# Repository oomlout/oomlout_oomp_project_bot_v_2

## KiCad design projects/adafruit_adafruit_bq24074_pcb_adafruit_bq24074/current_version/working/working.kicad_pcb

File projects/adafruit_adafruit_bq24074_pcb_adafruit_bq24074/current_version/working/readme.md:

# adafruit_bq24074_pcb
 
## summary 
* id: adafruit_adafruit_bq24074_pcb_adafruit_bq24074
* user: adafruit
* name: adafruit_bq24074_pcb
* board: adafruit_bq24074
* repo: https://github.com/adafruit/Adafruit-BQ24074-PCB

* src_file_repo_sch: 
* src_file_repo_sch_link: https://github.com/adafruit/Adafruit-BQ24074-PCB/tree/master/
* full details link: https://github.com/oomlout/oomlout_oomp_project_bot_v_2/tree/main/projects/adafruit_adafruit_bq24074_pcb_adafruit_bq24074/current_version/working  

## schematic  
  
[schematic (pdf)](working_schematic.pdf) 

## pcb  

[board (pdf)](working.pdf)  

## working_bom
| Id | Designator | Footprint | Quantity | Designation | Supplier and ref |  | None | 
| --- | --- | --- | --- | --- | --- | --- | --- | 
| 1 | D2,D4 | SMADIODE | 2 | SK34A |  |  | [''] | 
| 2 | FID3,FID1,FID2 | FIDUCIAL_1MM | 3 | FIDUCIAL_1MM |  |  | [''] | 
| 3 | UNK0.5A0,UNK1.5A0 | SOLDERJUMPER_ARROW_NOPASTE | 2 |  |  |  | [''] | 
| 4 | R10,R8,R11,R2,R7 | 0603-NO | 5 | 10K |  |  | [''] | 
| 5 | JP3 | 1X11_ROUND_76 | 1 |  |  |  | [''] | 
| 6 | X2 | USB_C_CUSB31-CFM2AX-01-X | 1 | USB Type C |  |  | [''] | 
| 7 | R9,R1 | 0603-NO | 2 | 1K |  |  | [''] | 
| 8 | R6,R4 | 0603-NO | 2 | 5.1K |  |  | [''] | 
| 9 | SYSOUT0,BATT0 | JST-PH-2-SMT-RA | 2 | JST 2PH |  |  | [''] | 
| 10 | U$14 | ADAFRUIT_5MM | 1 |  |  |  | [''] | 
| 11 | THERM0,UNK1A0 | SOLDERJUMPER_CLOSEDWIRE | 2 |  |  |  | [''] | 
| 12 | C1,C9,C5,C3,C6,C2,C4 | 0805-NO | 7 | 10uF |  |  | [''] | 
| 13 | R5 | 0603-NO | 1 | 2K |  |  | [''] | 
| 14 | R3 | 0603-NO | 1 | 590 |  |  | [''] | 
| 15 | U$11,U$3,U$12,U$4 | MOUNTINGHOLE_2.5_PLATED | 4 | MOUNTINGHOLE2.5 |  |  | [''] | 
| 16 | X3 | DCJACK_2MM_SMT | 1 | 2.1mm DC |  |  | [''] | 
| 17 | JP2,JP4 | 1X01_OVAL | 2 |  |  |  | [''] | 
| 18 | D3 | CHIPLED_0603 | 1 | RED |  |  | [''] | 
| 19 | X4 | QFN16_3MM | 1 | BQ24074 |  |  | [''] | 
| 20 | JP1 | 1X02_ROUND | 1 |  |  |  | [''] | 
| 21 | D1 | CHIPLED_0603 | 1 | GREEN |  |  | [''] | 
| 22 | SJ2,SJ1 | SOLDERJUMPER_2WAY_OPEN_NOPASTE | 2 |  |  |  | [''] | 
| 23 | U$18 | PCBFEAT-REV-040 | 1 |  |  |  | [''] | 

## bom_schematic
| Ref | Qnty | Value | Cmp name | Footprint | Description | Vendor | DNP | 
| --- | --- | --- | --- | --- | --- | --- | --- | 
| BATT0 | 1 | JST 2PH | JST_2PIN-SMT-RA | working:JST-PH-2-SMT-RA |  |  |  | 
| C1, C2, C3, C4, C5, C6, C9 | 7 | 10uF | CAP_CERAMIC0805-NOOUTLINE | working:0805-NO |  |  |  | 
| D1 | 1 | GREEN | LED0603 | working:CHIPLED_0603 |  |  |  | 
| D2, D4 | 2 | SK34A | DIODE-SCHOTTKYSMA | working:SMADIODE |  |  |  | 
| D3 | 1 | RED | LED0603 | working:CHIPLED_0603 |  |  |  | 
| FID1, FID2, FID3 | 3 | FIDUCIAL_1MM | FIDUCIAL_1MM | working:FIDUCIAL_1MM |  |  |  | 
| JP1 | 1 | HEADER-1X2ROUND | HEADER-1X2ROUND | working:1X02_ROUND |  |  |  | 
| JP2, JP4 | 2 | HEADER-1X1 | HEADER-1X1 | working:1X01_OVAL |  |  |  | 
| JP3 | 1 | HEADER-1X1176MIL | HEADER-1X1176MIL | working:1X11_ROUND_76 |  |  |  | 
| R1, R9 | 2 | 1K | RESISTOR_0603_NOOUT | working:0603-NO |  |  |  | 
| R2, R7, R8, R10, R11 | 5 | 10K | RESISTOR_0603_NOOUT | working:0603-NO |  |  |  | 
| R3 | 1 | 590 | RESISTOR_0603_NOOUT | working:0603-NO |  |  |  | 
| R4, R6 | 2 | 5.1K | RESISTOR_0603_NOOUT | working:0603-NO |  |  |  | 
| R5 | 1 | 2K | RESISTOR_0603_NOOUT | working:0603-NO |  |  |  | 
| SJ1, SJ2 | 2 | SOLDERJUMPER_2WAY | SOLDERJUMPER_2WAY | working:SOLDERJUMPER_2WAY_OPEN_NOPASTE |  |  |  | 
| SYSOUT0 | 1 | JST 2PH | JST_2PIN-SMT-RA | working:JST-PH-2-SMT-RA |  |  |  | 
| THERM0 | 1 | SOLDERJUMPERCLOSED | SOLDERJUMPERCLOSED | working:SOLDERJUMPER_CLOSEDWIRE |  |  |  | 
| U$3, U$4, U$11, U$12 | 4 | MOUNTINGHOLE2.5 | MOUNTINGHOLE2.5 | working:MOUNTINGHOLE_2.5_PLATED |  |  |  | 
| UNK0.5A0 | 1 | SOLDERJUMPER | SOLDERJUMPER | working:SOLDERJUMPER_ARROW_NOPASTE |  |  |  | 
| UNK1.5A0 | 1 | SOLDERJUMPER | SOLDERJUMPER | working:SOLDERJUMPER_ARROW_NOPASTE |  |  |  | 
| UNK1A0 | 1 | SOLDERJUMPERCLOSED | SOLDERJUMPERCLOSED | working:SOLDERJUMPER_CLOSEDWIRE |  |  |  | 
| X2 | 1 | USB Type C | USB_C | working:USB_C_CUSB31-CFM2AX-01-X |  |  |  | 
| X3 | 1 | 2.1mm DC | DCBARRELSMT | working:DCJACK_2MM_SMT |  |  |  | 
| X4 | 1 | BQ24074 | BQ24074 | working:QFN16_3MM |  |  |  | 

## mounting_holes
| x | y | package | value | ref | size | 
| --- | --- | --- | --- | --- | --- | 
| 0.0 | 0.0 | MOUNTINGHOLE_2.5_PLATED | MOUNTINGHOLE2.5 | U$3 | m3 | 
| 0.0 | 27.94 | MOUNTINGHOLE_2.5_PLATED | MOUNTINGHOLE2.5 | U$4 | m3 | 
| 33.02 | 27.94 | MOUNTINGHOLE_2.5_PLATED | MOUNTINGHOLE2.5 | U$11 | m3 | 
| 33.02 | 0.0 | MOUNTINGHOLE_2.5_PLATED | MOUNTINGHOLE2.5 | U$12 | m3 |

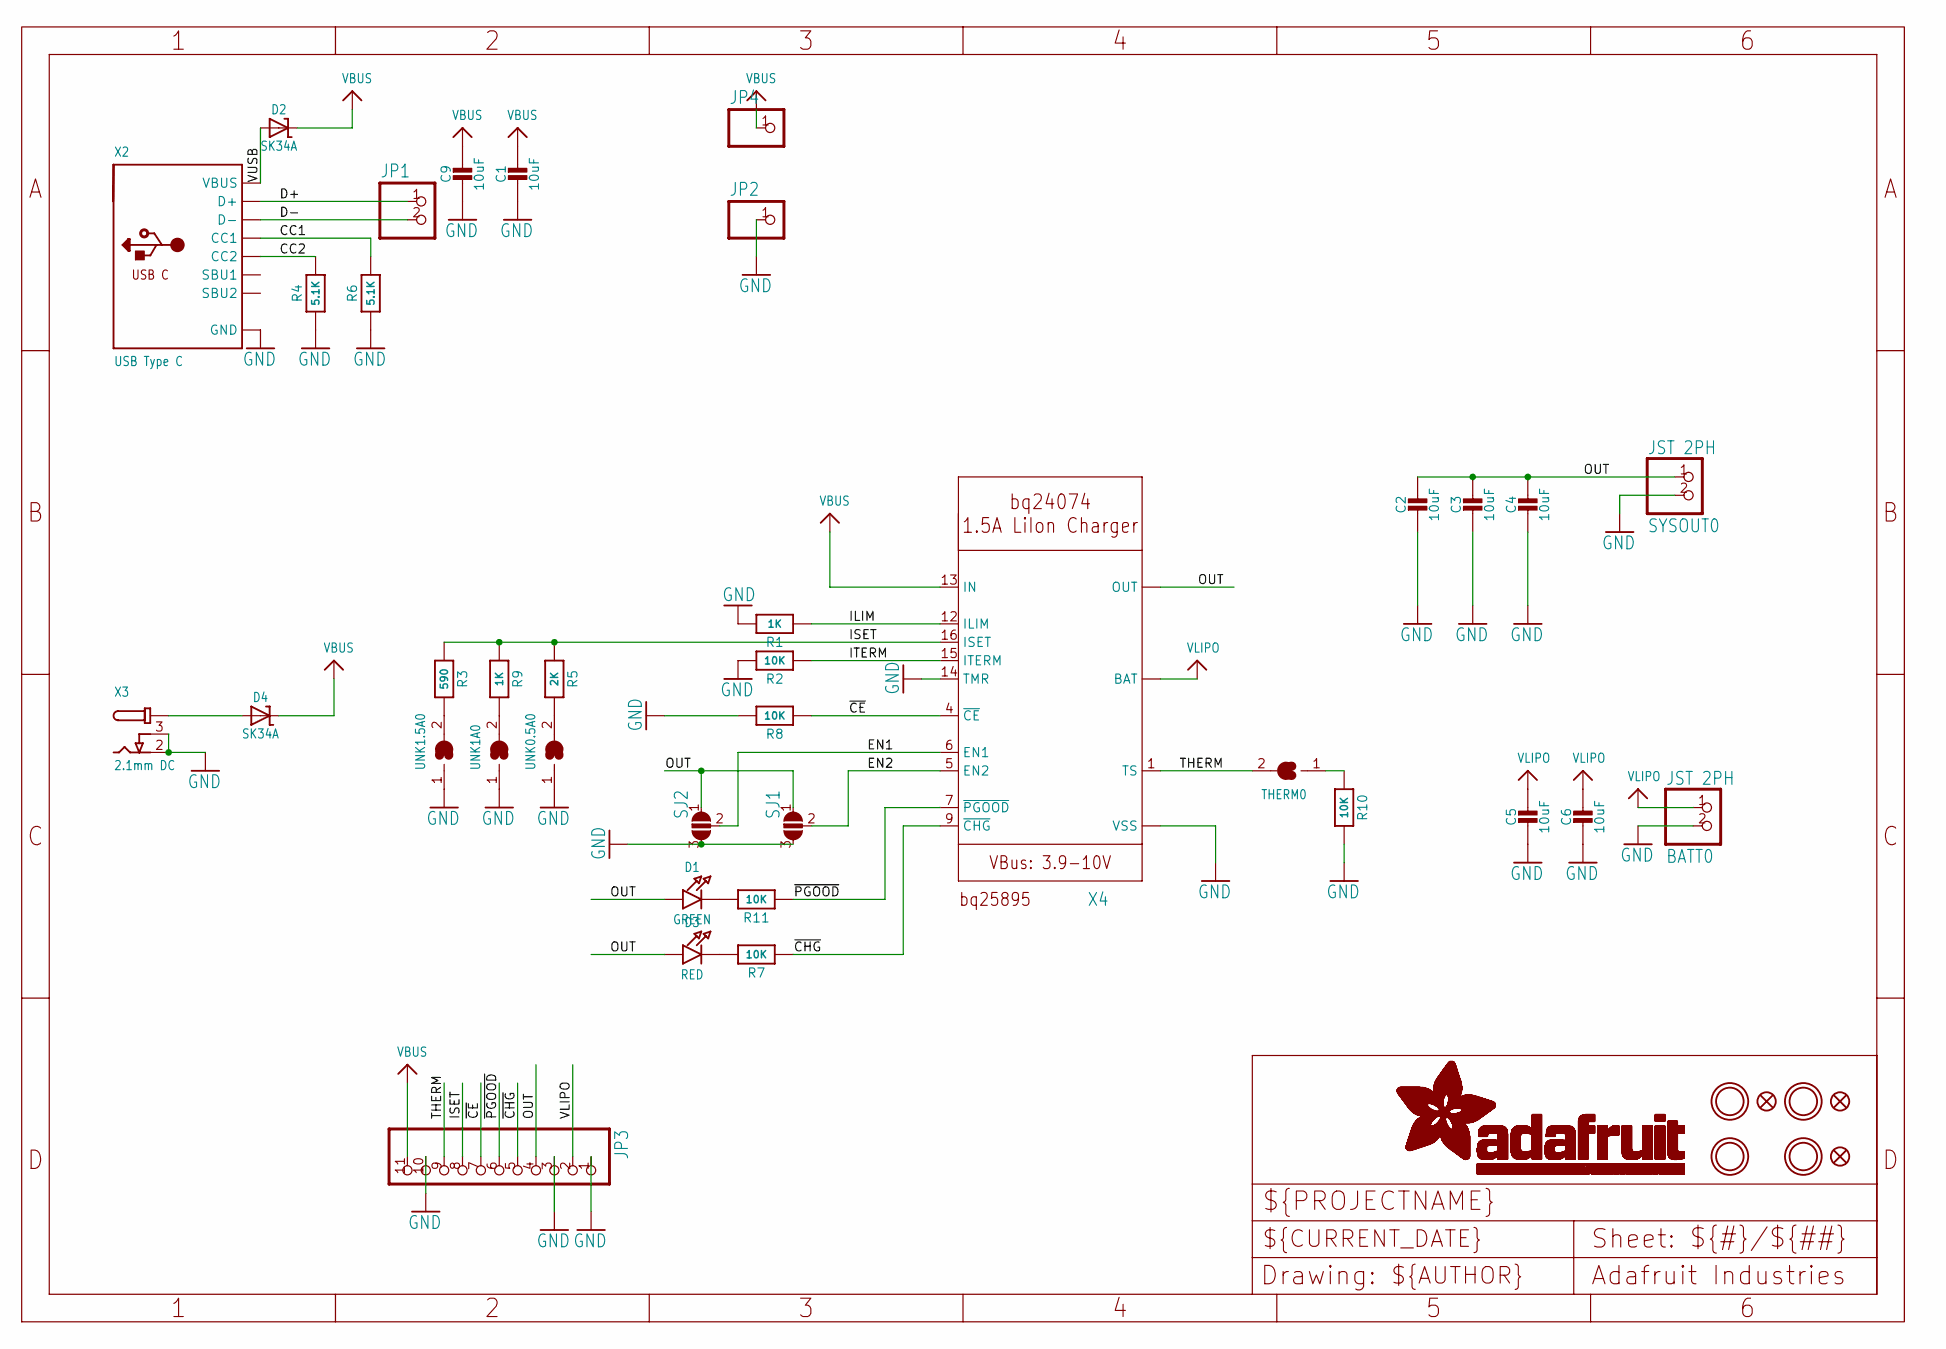
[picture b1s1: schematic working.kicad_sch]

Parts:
BATT0: JST 2PH; JST-PH-2-SMT-RA
C1, C2, C3, C4, C5, C6, C9: 10uF; 0805-NO
D1: GREEN; CHIPLED_0603
D2, D4: SK34A; SMADIODE
D3: RED; CHIPLED_0603
FID1, FID2, FID3: FIDUCIAL_1MM
JP1: HEADER-1X2ROUND; 1X02_ROUND
JP2, JP4: HEADER-1X1; 1X01_OVAL
JP3: HEADER-1X1176MIL; 1X11_ROUND_76
R1, R9: 1K; 0603-NO
R2, R7, R8, R10, R11: 10K; 0603-NO
R3: 590; 0603-NO
R4, R6: 5.1K; 0603-NO
R5: 2K; 0603-NO
SJ1, SJ2: SOLDERJUMPER_2WAY; SOLDERJUMPER_2WAY_OPEN_NOPASTE
SYSOUT0: JST 2PH; JST-PH-2-SMT-RA
THERM0: SOLDERJUMPERCLOSED; SOLDERJUMPER_CLOSEDWIRE
U$3, U$4, U$11, U$12: MOUNTINGHOLE2.5; MOUNTINGHOLE_2.5_PLATED
UNK0.5A0, UNK1.5A0: SOLDERJUMPER; SOLDERJUMPER_ARROW_NOPASTE
UNK1A0: SOLDERJUMPERCLOSED; SOLDERJUMPER_CLOSEDWIRE
X2: USB Type C; USB_C_CUSB31-CFM2AX-01-X
X3: 2.1mm DC; DCJACK_2MM_SMT
X4: BQ24074; QFN16_3MM

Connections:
CC1: R6.2, X2.A5 (CC1)
CC2: R4.2, X2.B5 (CC2)
D+: JP1.1, X2.A6 (D+), X2.B6 (D+)
D-: JP1.2, X2.A7 (D-), X2.B7 (D-)
EN1: SJ2.2, X4.6 (EN1)
EN2: SJ1.2, X4.5 (EN2)
GND: BATT0.2 (1), C1.2, C2.2, C3.2, C4.2, C5.2, C6.2, C9.2, JP2.1, JP3.1, JP3.3, JP3.10, R1.2, R2.2, R4.1, R6.1, R8.2, R10.2, SJ1.3, SJ2.3, SYSOUT0.2 (1), UNK0.5A0.1, UNK1.5A0.1, UNK1A0.1, X2.A1B12 (GND), X2.B1A12 (GND), X3.2 (GND), X3.3 (GNDBREAK), X4.8 (VSS), X4.14 (TMR), X4.THERMAL (VSS)
ILIM: R1.1, X4.12 (ILIM)
ISET: JP3.8, R3.1, R5.1, R9.1, X4.16 (ISET)
ITERM: R2.1, X4.15 (ITERM)
unnamed: D1.C, R11.2
unnamed: D4.A, X3.1 (PWR), X3.1' (PWR)
unnamed: D3.C, R7.2
unnamed: R3.2, UNK1.5A0.2
unnamed: R5.2, UNK0.5A0.2
unnamed: R9.2, UNK1A0.2
unnamed: R10.1, THERM0.1
OUT: C2.1, C3.1, C4.1, D1.A, D3.A, JP3.4, SJ1.1, SJ2.1, SYSOUT0.1 (2), X4.10 (OUT), X4.11 (OUT)
THERM: JP3.9, THERM0.2, X4.1 (TS)
VBUS: C1.1, C9.1, D2.C, D4.C, JP3.11, JP4.1, X4.13 (IN)
VLIPO: BATT0.1 (2), C5.1, C6.1, JP3.2, X4.2 (BAT), X4.3 (BAT)
VUSB: D2.A, X2.A4B9 (VBUS), X2.B4A9 (VBUS)
~CE: JP3.7, R8.1, X4.4 (~CE)
~CHG: JP3.5, R7.1, X4.9 (~CHG)
~PGOOD: JP3.6, R11.1, X4.7 (~PGOOD)

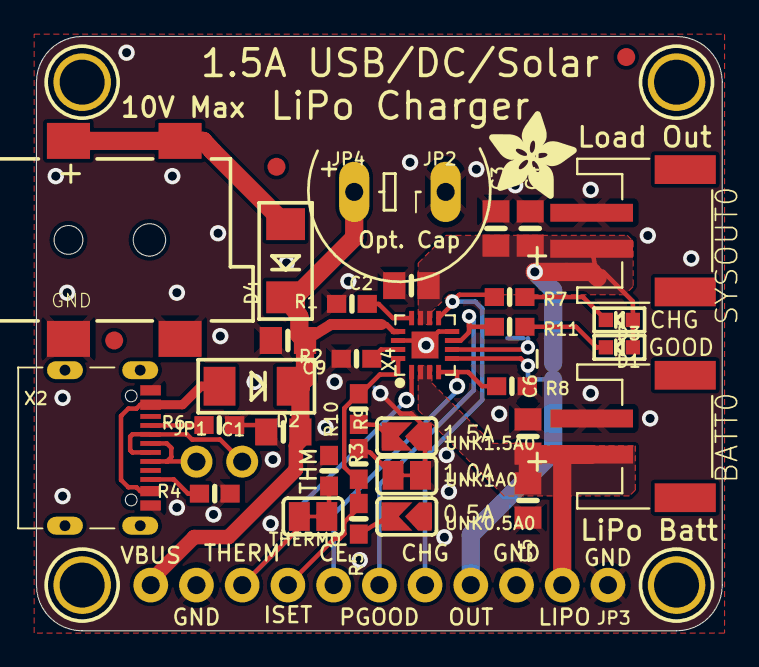
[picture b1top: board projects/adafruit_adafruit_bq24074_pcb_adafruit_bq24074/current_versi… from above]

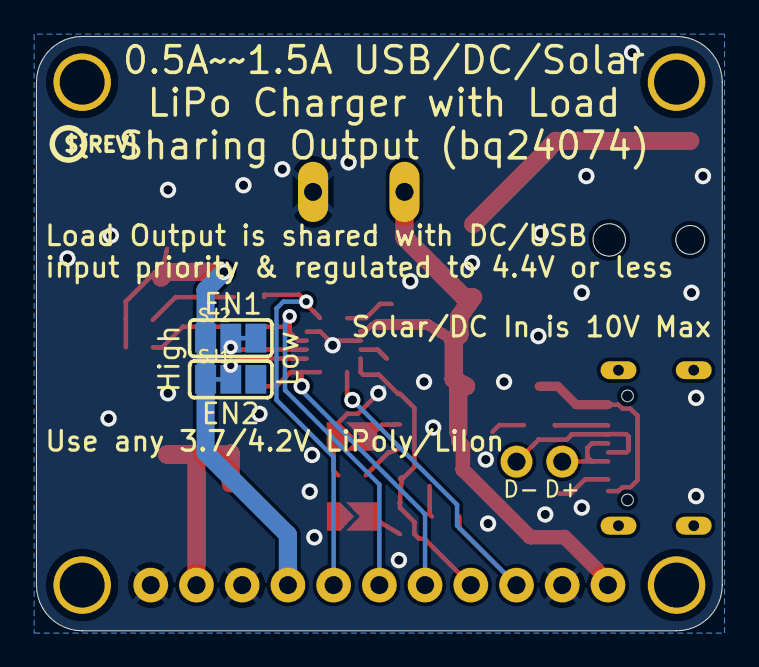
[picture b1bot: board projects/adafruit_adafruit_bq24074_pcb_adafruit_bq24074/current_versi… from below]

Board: 2 copper layers, 38.1 x 33.0 mm, 46 parts (3 on the bottom side), 25 nets.

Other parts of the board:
U$14: ADAFRUIT_5MM
U$18: PCBFEAT-REV-040

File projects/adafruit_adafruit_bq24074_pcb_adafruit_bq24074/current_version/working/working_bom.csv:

"Id";"Designator";"Footprint";"Quantity";"Designation";"Supplier and ref";
1;"D2,D4";"SMADIODE";2;"SK34A";;;
2;"FID3,FID1,FID2";"FIDUCIAL_1MM";3;"FIDUCIAL_1MM";;;
3;"UNK0.5A0,UNK1.5A0";"SOLDERJUMPER_ARROW_NOPASTE";2;"";;;
4;"R10,R8,R11,R2,R7";"0603-NO";5;"10K";;;
5;"JP3";"1X11_ROUND_76";1;"";;;
6;"X2";"USB_C_CUSB31-CFM2AX-01-X";1;"USB Type C";;;
7;"R9,R1";"0603-NO";2;"1K";;;
8;"R6,R4";"0603-NO";2;"5.1K";;;
9;"SYSOUT0,BATT0";"JST-PH-2-SMT-RA";2;"JST 2PH";;;
10;"U$14";"ADAFRUIT_5MM";1;"";;;
11;"THERM0,UNK1A0";"SOLDERJUMPER_CLOSEDWIRE";2;"";;;
12;"C1,C9,C5,C3,C6,C2,C4";"0805-NO";7;"10uF";;;
13;"R5";"0603-NO";1;"2K";;;
14;"R3";"0603-NO";1;"590";;;
15;"U$11,U$3,U$12,U$4";"MOUNTINGHOLE_2.5_PLATED";4;"MOUNTINGHOLE2.5";;;
16;"X3";"DCJACK_2MM_SMT";1;"2.1mm DC";;;
17;"JP2,JP4";"1X01_OVAL";2;"";;;
18;"D3";"CHIPLED_0603";1;"RED";;;
19;"X4";"QFN16_3MM";1;"BQ24074";;;
20;"JP1";"1X02_ROUND";1;"";;;
21;"D1";"CHIPLED_0603";1;"GREEN";;;
22;"SJ2,SJ1";"SOLDERJUMPER_2WAY_OPEN_NOPASTE";2;"";;;
23;"U$18";"PCBFEAT-REV-040";1;"";;;

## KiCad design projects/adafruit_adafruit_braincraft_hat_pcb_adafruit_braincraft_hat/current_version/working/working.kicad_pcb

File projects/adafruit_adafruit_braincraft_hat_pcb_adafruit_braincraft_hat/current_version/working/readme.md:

# adafruit_braincraft_hat_pcb
 
## summary 
* id: adafruit_adafruit_braincraft_hat_pcb_adafruit_braincraft_hat
* user: adafruit
* name: adafruit_braincraft_hat_pcb
* board: adafruit_braincraft_hat
* repo: https://github.com/adafruit/Adafruit-BrainCraft-HAT-PCB

* src_file_repo_sch: 
* src_file_repo_sch_link: https://github.com/adafruit/Adafruit-BrainCraft-HAT-PCB/tree/main/
* full details link: https://github.com/oomlout/oomlout_oomp_project_bot_v_2/tree/main/projects/adafruit_adafruit_braincraft_hat_pcb_adafruit_braincraft_hat/current_version/working  

## schematic  
  
[schematic (pdf)](working_schematic.pdf) 

## pcb  

[board (pdf)](working.pdf)  

## working_bom
| Id | Designator | Footprint | Quantity | Designation | Supplier and ref |  | None | 
| --- | --- | --- | --- | --- | --- | --- | --- | 
| 1 | FID2,FID1 | FIDUCIAL_1MM | 2 | FIDUCIAL_1MM |  |  | [''] | 
| 2 | U$72 | STEMMAQT | 1 |  |  |  | [''] | 
| 3 | U$11 | PCBFEAT-REV-040 | 1 |  |  |  | [''] | 
| 4 | HEADPHONE0 | 4UCONN_18510 | 1 |  |  |  | [''] | 
| 5 | SW1 | EVQ-Q2_SMALLER | 1 | EVQQ |  |  | [''] | 
| 6 | X5,X1 | JSTPH2 | 2 | JSTPH 2P |  |  | [''] | 
| 7 | SENSE0,NEOPIX0 | JSTPH3 | 2 | JST PH 3 |  |  | [''] | 
| 8 | SW6 | EG1390 | 1 | EG1390 |  |  | [''] | 
| 9 | LEFTMIC0,RIGHTMIC0 | SPW2430HR5H-B | 2 |  |  |  | [''] | 
| 10 | C4,C6 | PANASONIC_C | 2 | 100uF |  |  | [''] | 
| 11 | U$75 | ADAFRUIT_5MM | 1 |  |  |  | [''] | 
| 12 | LED2,LED1,LED3 | APA102 | 3 | SK6822 |  |  | [''] | 
| 13 | CONN3 | JST_SH4 | 1 | STEMMA_I2C_QT |  |  | [''] | 
| 14 | SW5 | SKQUBAE010 | 1 | NAVSWITCHSKQUABAUE010 |  |  | [''] | 
| 15 | RPI1 | PI_HAT_SMTTHM_SLOTS | 1 | RASPBERRYPI_BPLUS_HAT_SMTTHM_SLOTS |  |  | [''] | 
| 16 | JP4,JP5 | 1X03_ROUND_76 | 2 |  |  |  | [''] | 
| 17 | CONN1 | 1X25_ROUND_70MIL | 1 | HEADER-1X25 |  |  | [''] | 
| 18 | TFT2 | TFT_1.54IN_240X240_22PIN | 1 | DISP_TFT_1.54IN_240X240_22P |  |  | [''] | 
| 19 | D1,D2 | SOD-323 | 2 | 3.6V |  |  | [''] | 
| 20 | C1,C24,C9,C5,C11,C32,C23,C10,C17,C34,C33,C13,C15,C2 | 0805-NO | 14 | 10uF |  |  | [''] | 
| 21 | U$87 | ADAFRUIT_9MM | 1 |  |  |  | [''] | 
| 22 | Q3,Q1 | SOT23-WIDE | 2 | BSS138 |  |  | [''] | 
| 23 | R7,R8 | 0603-NO | 2 | 1K |  |  | [''] | 
| 24 | C3,C12,C7,C16,C18,C14,C8,C25 | 0603-NO | 8 | 0.1uF |  |  | [''] | 
| 25 | D3 | SOD-323 | 1 | 1N4148 |  |  | [''] | 
| 26 | C19,C21,C22,C20 | 0603-NO | 4 | 33pF |  |  | [''] | 
| 27 | FB2,FB1 | 0805 | 2 | Ferrite |  |  | [''] | 
| 28 | R1,R4,R2,R3 | 0603-NO | 4 | 10K |  |  | [''] | 
| 29 | IC4 | SOT23 | 1 | APX803-SAG |  |  | [''] | 
| 30 | R6 | 0603-NO | 1 | 10k |  |  | [''] | 
| 31 | TP2,TP3,TP1,TP4 | SMT_NUT_3MM | 4 | SEWTAP_SMTNUTM3 |  |  | [''] | 
| 32 | C27,C26 | 0603-NO | 2 | 220pF |  |  | [''] | 
| 33 | FB7,FB3,FB9,FB8,FB10 | 0805-NO | 5 | Ferrite |  |  | [''] | 
| 34 | U3 | SOT23-5 | 1 | AP2112-3.3K |  |  | [''] | 
| 35 | R5 | 0603-NO | 1 | 10 |  |  | [''] | 
| 36 | R10,R9 | RESPACK_4X0603 | 2 | 10K |  |  | [''] | 
| 37 | OSC1 | OSC_3.2X2.5MM | 1 | ECS-3225MV |  |  | [''] | 
| 38 | FB4 | 0805-NO | 1 | FERRITE |  |  | [''] | 
| 39 | C29,C30,C28,C31 | 0603-NO | 4 | 100pF |  |  | [''] | 
| 40 | SJ1 | SOLDERJUMPER_2WAY_OPEN_NOPASTE | 1 |  |  |  | [''] | 
| 41 | IC3 | QFN32_5MM | 1 | WM8960 |  |  | [''] | 
| 42 | TP6 | TESTPOINT_ROUND_2MM | 1 |  |  |  | [''] | 
| 43 | U$79 | BRAINPAD_1IN | 1 |  |  |  | [''] | 
| 44 | U$82 | FAN_30X30MM | 1 |  |  |  | [''] | 
| 45 | U$84 | 53398-0271 | 1 | CON_MOLEX_2P |  |  | [''] | 

## bom_schematic
no data

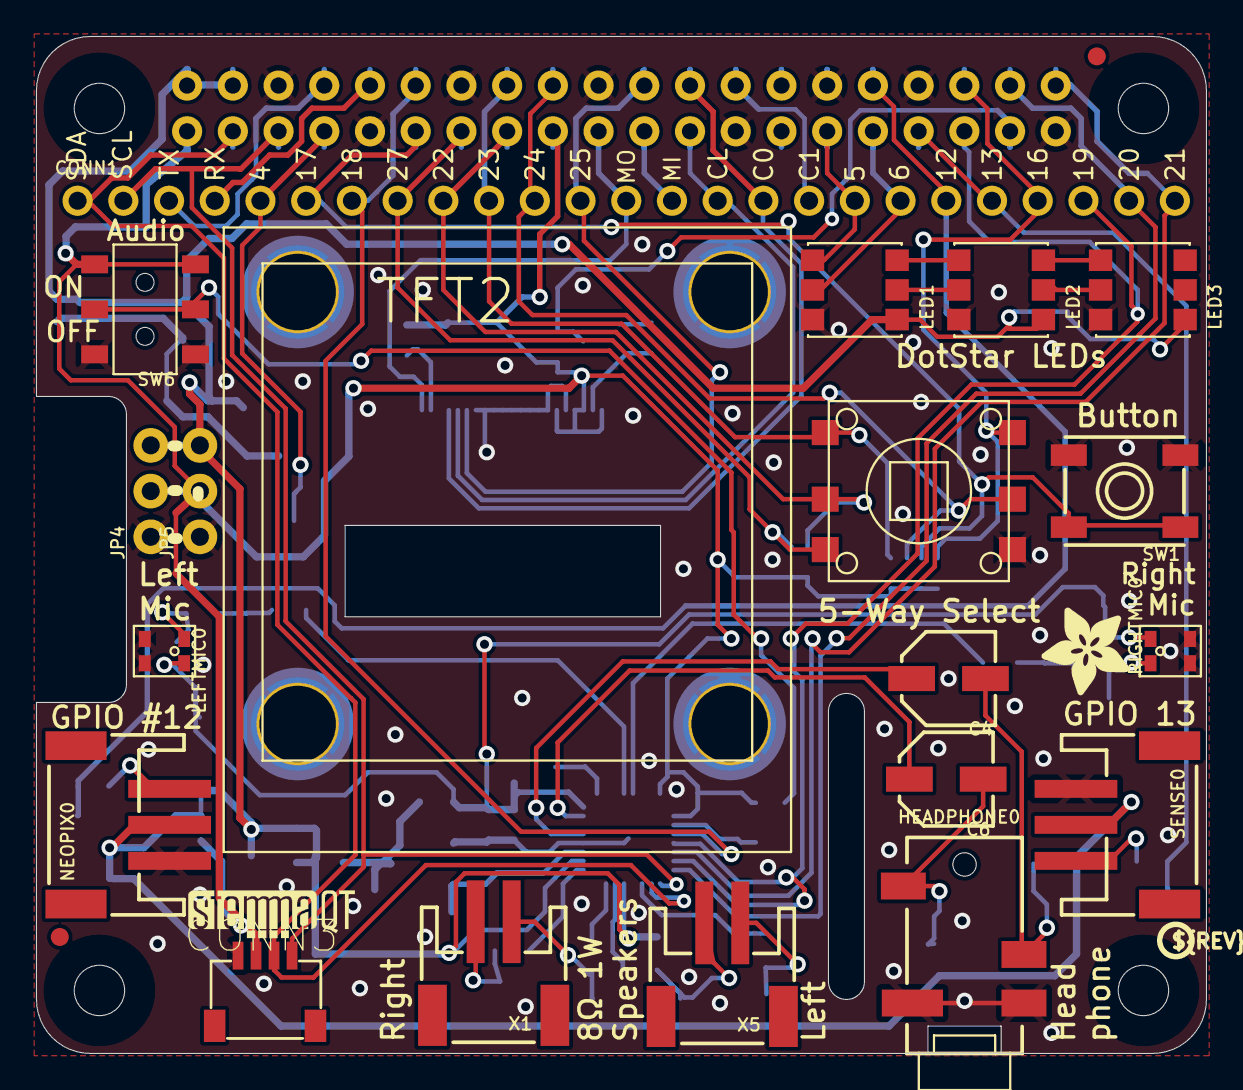
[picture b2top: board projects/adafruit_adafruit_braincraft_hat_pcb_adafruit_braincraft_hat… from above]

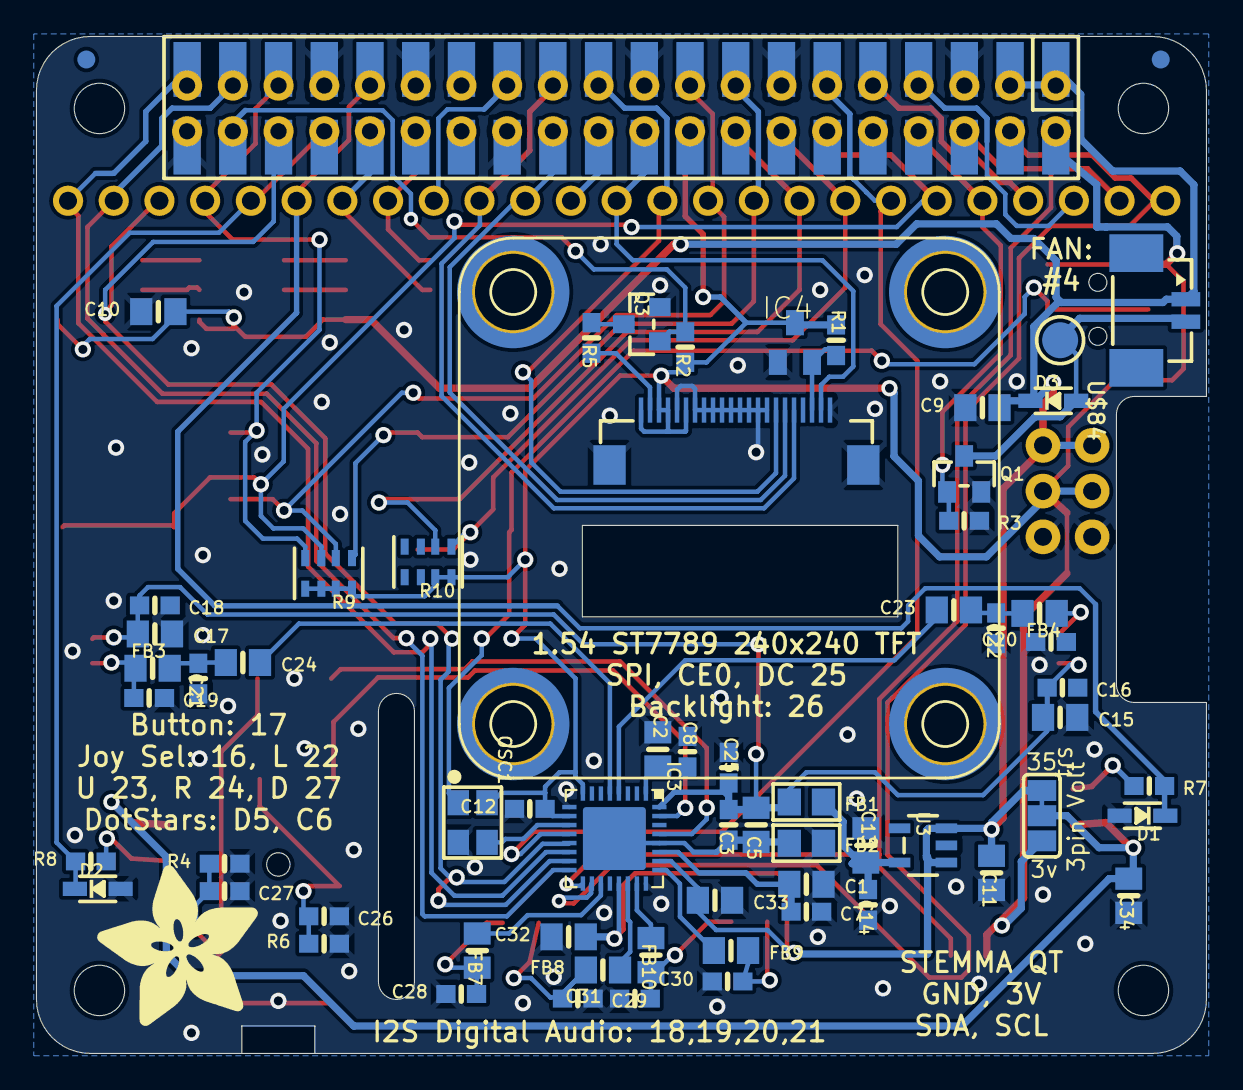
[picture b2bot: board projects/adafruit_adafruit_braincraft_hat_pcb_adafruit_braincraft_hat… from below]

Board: 2 copper layers, 65.0 x 56.5 mm, 95 parts (69 on the bottom side), 67 nets.

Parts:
C1, C2, C5, C9, C10, C11, C13, C15, C17, C23, C24, C32, C33, C34: 10uF; 0805-NO
C3, C7, C8, C12, C14, C16, C18, C25: 0.1uF; 0603-NO
C4, C6: 100uF; PANASONIC_C
C19, C20, C21, C22: 33pF; 0603-NO
C26, C27: 220pF; 0603-NO
C28, C29, C30, C31: 100pF; 0603-NO
CONN1: HEADER-1X25; 1X25_ROUND_70MIL
CONN3: STEMMA_I2C_QT; JST_SH4
D1, D2: 3.6V; SOD-323
D3: 1N4148; SOD-323
FB1, FB2: Ferrite; 0805
FB3, FB7, FB8, FB9, FB10: Ferrite; 0805-NO
FB4: FERRITE; 0805-NO
FID1, FID2: FIDUCIAL_1MM
HEADPHONE0: 4UCONN_18510
IC3: WM8960; QFN32_5MM
IC4: APX803-SAG; SOT23
JP4, JP5: 1X03_ROUND_76
LED1, LED2, LED3: SK6822; APA102
LEFTMIC0: SPW2430HR5H-B
NEOPIX0: JST PH 3; JSTPH3
OSC1: ECS-3225MV; OSC_3.2X2.5MM
Q1, Q3: BSS138; SOT23-WIDE
R1, R2, R3, R4: 10K; 0603-NO
R5: 10; 0603-NO
R6: 10k; 0603-NO
R7, R8: 1K; 0603-NO
R9, R10: 10K; RESPACK_4X0603
RIGHTMIC0: SPW2430HR5H-B
RPI1: RASPBERRYPI_BPLUS_HAT_SMTTHM_SLOTS; PI_HAT_SMTTHM_SLOTS
SENSE0: JST PH 3; JSTPH3
SJ1: SOLDERJUMPER_2WAY_OPEN_NOPASTE
SW1: EVQQ; EVQ-Q2_SMALLER
SW5: NAVSWITCHSKQUABAUE010; SKQUBAE010
SW6: EG1390
TFT2: DISP_TFT_1.54IN_240X240_22P; TFT_1.54IN_240X240_22PIN
TP1, TP2, TP3, TP4: SEWTAP_SMTNUTM3; SMT_NUT_3MM
TP6: TESTPOINT_ROUND_2MM
U3: AP2112-3.3K; SOT23-5
U$11: PCBFEAT-REV-040
U$72: STEMMAQT
U$75: ADAFRUIT_5MM
U$79: BRAINPAD_1IN
U$82: FAN_30X30MM
U$84: CON_MOLEX_2P; 53398-0271
U$87: ADAFRUIT_9MM
X1, X5: JSTPH 2P; JSTPH2

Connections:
3.3V: C12.1, CONN3.2, IC3.8, IC3.10, IC4.3, JP4.2, JP5.2, OSC1.4, R1.2, R2.2, R9.5, R9.6, R9.7, R9.8, R10.7, R10.8, RPI1.1, RPI1.17, RPI1.S1, RPI1.S17, SJ1.3, SW6.S1, SW6.S2, TFT2.1, TFT2.3, TFT2.4, TFT2.6
5.0V: C9.1, C10.1, C11.1, C32.1, C33.1, D3.C, IC3.21, IC3.26, JP4.3, JP5.3, LED1.4, LED2.4, LED3.4, RPI1.2, RPI1.4, RPI1.S2, RPI1.S4, SJ1.1, U3.1, U3.3, U$84.1
AGND: C3.2, C5.2, FB2.1, IC3.28, IC3.33
AVDD: C3.1, C5.1, C15.1, C16.1, C17.1, C18.1, C25.1, FB1.1, IC3.32, LEFTMIC0.4, RIGHTMIC0.4
BUTTON: CONN1.6, R9.3, RPI1.11, RPI1.S11, SW1.B, SW1.B'
EECLK: RPI1.28, RPI1.S28
EEDATA: RPI1.27, RPI1.S27
FAN: CONN1.5, Q1.1, R3.1, RPI1.7, RPI1.S7
GND: C1.2, C2.2, C7.2, C8.2, C9.2, C10.2, C11.2, C12.2, C13.2, C14.2, C15.2, C16.2, C17.2, C18.2, C19.2, C20.2, C21.2, C22.2, C25.2, C26.2, C27.2, C28.2, C29.2, C30.2, C31.2, C32.2, C33.2, C34.2, CONN3.1, D1.A, D2.A, FB2.2, HEADPHONE0.1-GND, HEADPHONE0.4-INNER_SLEEVE, IC3.9, IC3.20, IC3.24, IC4.1, JP4.1, JP5.1, LED1.3, LED2.3, LED3.3, LEFTMIC0.2, LEFTMIC0.3, NEOPIX0.1, OSC1.2, Q1.2, Q3.2, R3.2, R4.1, R6.1, RIGHTMIC0.2, RIGHTMIC0.3, RPI1.6, RPI1.9, RPI1.14, RPI1.20, RPI1.25, RPI1.30, RPI1.34, RPI1.39, RPI1.S6, RPI1.S9, RPI1.S14, RPI1.S20, RPI1.S25, RPI1.S30, RPI1.S34, RPI1.S39, SENSE0.1, SW1.A, SW1.A', SW5.4, SW6.O1, SW6.O2, TFT2.5, TFT2.7, TFT2.8, TFT2.9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
I2S_BCLK: CONN1.7, IC3.12, RPI1.12, RPI1.S12
I2S_DIN: CONN1.24, IC3.16, RPI1.38, RPI1.S38
I2S_DOUT: CONN1.25, IC3.14, RPI1.40, RPI1.S40
I2S_LRCLK: CONN1.23, IC3.13, IC3.15, RPI1.35, RPI1.S35
JOY_D: CONN1.8, R10.1, RPI1.13, RPI1.S13, SW5.3
JOY_IN: CONN1.22, R9.4, RPI1.36, RPI1.S36, SW5.6
JOY_L: CONN1.9, R10.2, RPI1.15, RPI1.S15, SW5.2
JOY_R: CONN1.11, R9.2, RPI1.18, RPI1.S18, SW5.5
JOY_U: CONN1.10, R9.1, RPI1.16, RPI1.S16, SW5.1
LEDC: CONN1.19, LED1.2, RPI1.31, RPI1.S31
LEDD: CONN1.18, LED1.1, RPI1.29, RPI1.S29
LEDK: R5.2, TFT2.2
LINPUT1: C23.2, IC3.4
LITE: Q3.1, R2.1, RPI1.37, RPI1.S37
LSTEMMA: NEOPIX0.3, R7.1
MCLK: IC3.11, OSC1.3
MCLK_EN: OSC1.1, SW6.P1, SW6.P2
MICBIAS: C2.1, C8.1, IC3.1
unnamed: FB7.1, IC3.19
unnamed: FB8.1, IC3.22
unnamed: C6.+, IC3.31
unnamed: Q3.3, R5.1
unnamed: C4.+, IC3.29
unnamed: LED1.6, LED2.1
unnamed: C4.-, C27.1, HEADPHONE0.3-OUTER_SLEEVE, R4.2
unnamed: C6.-, C26.1, HEADPHONE0.2-TIP, R6.2
unnamed: LED1.5, LED2.2
unnamed: C19.1, FB3.1, RIGHTMIC0.1
unnamed: C20.1, FB4.1, LEFTMIC0.1
unnamed: LED2.6, LED3.1
unnamed: LED2.5, LED3.2
unnamed: C21.1, C24.1, FB3.2
unnamed: C22.1, C23.1, FB4.2
unnamed: D3.A, Q1.3, TP6.P$1, U$84.2
unnamed: FB9.1, IC3.25
unnamed: FB10.1, IC3.23
OUT: C13.1, C14.1, FB1.2, U3.5
PWM0: CONN1.20, D1.C, R7.2, RPI1.32, RPI1.S32
PWM1: CONN1.21, D2.C, R8.2, RPI1.33, RPI1.S33
RINPUT1: C24.2, IC3.5
RSTEMMA: R8.1, SENSE0.3
RXD: CONN1.4, RPI1.10, RPI1.S10
SCL: CONN1.2, CONN3.4, IC3.17, RPI1.5, RPI1.S5
SDA: CONN1.1, CONN3.3, IC3.18, RPI1.3, RPI1.S3
SPI_CE1: CONN1.17, RPI1.26, RPI1.S26
SPI_MISO: CONN1.14, RPI1.21, RPI1.S21
SPK_LN: C31.1, FB10.2, X1.1
SPK_LP: C30.1, FB9.2, X1.2
SPK_RN: C28.1, FB7.2, X5.1
SPK_RP: C29.1, FB8.2, X5.2
TFT_CS: CONN1.16, RPI1.24, RPI1.S24, TFT2.18
TFT_DC: CONN1.12, RPI1.22, RPI1.S22, TFT2.16
TFT_MOSI: CONN1.13, RPI1.19, RPI1.S19, TFT2.21
TFT_RESET: IC4.2, R1.1, TFT2.20
TFT_SCLK: CONN1.15, RPI1.23, RPI1.S23, TFT2.17
TXD: CONN1.3, RPI1.8, RPI1.S8
VCC: C34.1, NEOPIX0.2, SENSE0.2, SJ1.2
VMID: C1.1, C7.1, IC3.27

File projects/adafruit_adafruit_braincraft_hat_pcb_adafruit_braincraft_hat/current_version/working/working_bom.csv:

"Id";"Designator";"Footprint";"Quantity";"Designation";"Supplier and ref";
1;"FID2,FID1";"FIDUCIAL_1MM";2;"FIDUCIAL_1MM";;;
2;"U$72";"STEMMAQT";1;"";;;
3;"U$11";"PCBFEAT-REV-040";1;"";;;
4;"HEADPHONE0";"4UCONN_18510";1;"";;;
5;"SW1";"EVQ-Q2_SMALLER";1;"EVQQ";;;
6;"X5,X1";"JSTPH2";2;"JSTPH 2P";;;
7;"SENSE0,NEOPIX0";"JSTPH3";2;"JST PH 3";;;
8;"SW6";"EG1390";1;"EG1390";;;
9;"LEFTMIC0,RIGHTMIC0";"SPW2430HR5H-B";2;"";;;
10;"C4,C6";"PANASONIC_C";2;"100uF";;;
11;"U$75";"ADAFRUIT_5MM";1;"";;;
12;"LED2,LED1,LED3";"APA102";3;"SK6822";;;
13;"CONN3";"JST_SH4";1;"STEMMA_I2C_QT";;;
14;"SW5";"SKQUBAE010";1;"NAVSWITCHSKQUABAUE010";;;
15;"RPI1";"PI_HAT_SMTTHM_SLOTS";1;"RASPBERRYPI_BPLUS_HAT_SMTTHM_SLOTS";;;
16;"JP4,JP5";"1X03_ROUND_76";2;"";;;
17;"CONN1";"1X25_ROUND_70MIL";1;"HEADER-1X25";;;
18;"TFT2";"TFT_1.54IN_240X240_22PIN";1;"DISP_TFT_1.54IN_240X240_22P";;;
19;"D1,D2";"SOD-323";2;"3.6V";;;
20;"C1,C24,C9,C5,C11,C32,C23,C10,C17,C34,C33,C13,C15,C2";"0805-NO";14;"10uF";;;
21;"U$87";"ADAFRUIT_9MM";1;"";;;
22;"Q3,Q1";"SOT23-WIDE";2;"BSS138";;;
23;"R7,R8";"0603-NO";2;"1K";;;
24;"C3,C12,C7,C16,C18,C14,C8,C25";"0603-NO";8;"0.1uF";;;
25;"D3";"SOD-323";1;"1N4148";;;
26;"C19,C21,C22,C20";"0603-NO";4;"33pF";;;
27;"FB2,FB1";"0805";2;"Ferrite";;;
28;"R1,R4,R2,R3";"0603-NO";4;"10K";;;
29;"IC4";"SOT23";1;"APX803-SAG";;;
30;"R6";"0603-NO";1;"10k";;;
31;"TP2,TP3,TP1,TP4";"SMT_NUT_3MM";4;"SEWTAP_SMTNUTM3";;;
32;"C27,C26";"0603-NO";2;"220pF";;;
33;"FB7,FB3,FB9,FB8,FB10";"0805-NO";5;"Ferrite";;;
34;"U3";"SOT23-5";1;"AP2112-3.3K";;;
35;"R5";"0603-NO";1;"10";;;
36;"R10,R9";"RESPACK_4X0603";2;"10K";;;
37;"OSC1";"OSC_3.2X2.5MM";1;"ECS-3225MV";;;
38;"FB4";"0805-NO";1;"FERRITE";;;
39;"C29,C30,C28,C31";"0603-NO";4;"100pF";;;
40;"SJ1";"SOLDERJUMPER_2WAY_OPEN_NOPASTE";1;"";;;
41;"IC3";"QFN32_5MM";1;"WM8960";;;
42;"TP6";"TESTPOINT_ROUND_2MM";1;"";;;
43;"U$79";"BRAINPAD_1IN";1;"";;;
44;"U$82";"FAN_30X30MM";1;"";;;
45;"U$84";"53398-0271";1;"CON_MOLEX_2P";;;

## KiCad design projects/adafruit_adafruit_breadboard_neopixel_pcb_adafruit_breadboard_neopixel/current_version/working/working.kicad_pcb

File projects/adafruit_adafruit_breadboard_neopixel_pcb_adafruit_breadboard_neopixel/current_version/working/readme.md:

# adafruit_breadboard_neopixel_pcb
 
## summary 
* id: adafruit_adafruit_breadboard_neopixel_pcb_adafruit_breadboard_neopixel
* user: adafruit
* name: adafruit_breadboard_neopixel_pcb
* board: adafruit_breadboard_neopixel
* repo: https://github.com/adafruit/Adafruit_Breadboard_NeoPixel_PCB

* src_file_repo_sch: 
* src_file_repo_sch_link: https://github.com/adafruit/Adafruit_Breadboard_NeoPixel_PCB/tree/master/
* full details link: https://github.com/oomlout/oomlout_oomp_project_bot_v_2/tree/main/projects/adafruit_adafruit_breadboard_neopixel_pcb_adafruit_breadboard_neopixel/current_version/working  

## schematic  
  
[schematic (pdf)](working_schematic.pdf) 

## pcb  

[board (pdf)](working.pdf)  

## working_bom
| Id | Designator | Footprint | Quantity | Designation | Supplier and ref |  | None | 
| --- | --- | --- | --- | --- | --- | --- | --- | 
| 1 | @HOLE1,@HOLE0 |  | 2 |  |  |  | [''] | 
| 2 | JP2,JP1 | 1X03-CLEANBIG | 2 |  |  |  | [''] | 
| 3 | LED1 | WS28115050 | 1 | WS28115050 |  |  | [''] | 
| 4 | R1 | R0603 | 1 | 1.0K |  |  | [''] | 
| 5 | R3,R2 | R0603 | 2 | 22 |  |  | [''] | 
| 6 | C1 | C0603K | 1 | 1uF |  |  | [''] | 
| 7 | U$1 | ADAFRUIT_2.5MM | 1 |  |  |  | [''] | 

## bom_schematic
| Ref | Qnty | Value | Cmp name | Footprint | Description | Vendor | DNP | 
| --- | --- | --- | --- | --- | --- | --- | --- | 
| C1 | 1 | 1uF | C-USC0603K | working:C0603K |  |  |  | 
| JP1, JP2 | 2 | PINHD-1X3CB | PINHD-1X3CB | working:1X03-CLEANBIG |  |  |  | 
| LED1 | 1 | WS28115050 | WS28115050 | working:WS28115050 |  |  |  | 
| R1 | 1 | 1.0K | R-US_R0603 | working:R0603 |  |  |  | 
| R2, R3 | 2 | 22 | R-US_R0603 | working:R0603 |  |  |  |

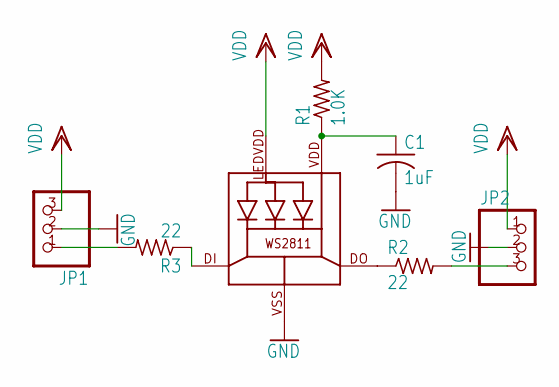
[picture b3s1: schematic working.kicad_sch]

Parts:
C1: 1uF; C0603K
JP1, JP2: PINHD-1X3CB; 1X03-CLEANBIG
LED1: WS28115050
R1: 1.0K; R0603
R2, R3: 22; R0603

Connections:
GND: C1.2, JP1.2, JP2.2, LED1.VSS (GND)
IN: JP1.1, R3.2
unnamed: LED1.DO, R2.1
unnamed: LED1.DI, R3.1
unnamed: C1.1, LED1.VDD, R1.1
OUT: JP2.3, R2.2
VDD: JP1.3, JP2.1, LED1.LEDVDD, R1.2

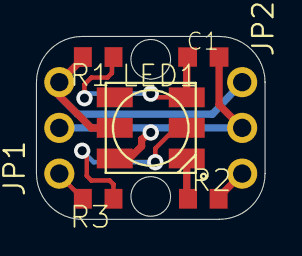
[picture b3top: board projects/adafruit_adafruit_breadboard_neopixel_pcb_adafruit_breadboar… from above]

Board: 16 copper layers, 12.7 x 10.2 mm, 10 parts (1 on the bottom side), 7 nets.

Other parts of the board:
@HOLE0, @HOLE1: (no value)
U$1: ADAFRUIT_2.5MM

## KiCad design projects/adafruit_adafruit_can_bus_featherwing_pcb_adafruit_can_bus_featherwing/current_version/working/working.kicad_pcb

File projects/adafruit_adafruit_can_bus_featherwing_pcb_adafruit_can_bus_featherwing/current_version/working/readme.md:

# adafruit_can_bus_featherwing_pcb
 
## summary 
* id: adafruit_adafruit_can_bus_featherwing_pcb_adafruit_can_bus_featherwing
* user: adafruit
* name: adafruit_can_bus_featherwing_pcb
* board: adafruit_can_bus_featherwing
* repo: https://github.com/adafruit/Adafruit-CAN-Bus-FeatherWing-PCB

* src_file_repo_sch: 
* src_file_repo_sch_link: https://github.com/adafruit/Adafruit-CAN-Bus-FeatherWing-PCB/tree/main/
* full details link: https://github.com/oomlout/oomlout_oomp_project_bot_v_2/tree/main/projects/adafruit_adafruit_can_bus_featherwing_pcb_adafruit_can_bus_featherwing/current_version/working  

## schematic  
  
[schematic (pdf)](working_schematic.pdf) 

## pcb  

[board (pdf)](working.pdf)  

## working_bom
| Id | Designator | Footprint | Quantity | Designation | Supplier and ref |  | None | 
| --- | --- | --- | --- | --- | --- | --- | --- | 
| 1 | C8,C7 | 0603-NO | 2 | 15pF |  |  | [''] | 
| 2 | IC2 | SOIC18WIDE | 1 | MCP2515/SO |  |  | [''] | 
| 3 | C10,C22,C11 | 0603-NO | 3 | 0.1uF |  |  | [''] | 
| 4 | JP4 | 1X04_ROUND | 1 |  |  |  | [''] | 
| 5 | PLABEL15 | PLABEL15 | 1 |  |  |  | [''] | 
| 6 | NEOPIX1 | TERMBLOCK_1X3-3.5MM | 1 | 3.5mm |  |  | [''] | 
| 7 | U1 | SOT23-6 | 1 | AP3602 |  |  | [''] | 
| 8 | C14,C12,C2,C1 | 0805-NO | 4 | 10uF |  |  | [''] | 
| 9 | FID2,FID3 | FIDUCIAL_1MM | 2 | FIDUCIAL_1MM |  |  | [''] | 
| 10 | Y1 | CRYSTAL_3.2X2.5 | 1 | 16MHz 9pF |  |  | [''] | 
| 11 | PLABEL2 | PLABEL2 | 1 |  |  |  | [''] | 
| 12 | U$21 | SYMBOL_MINUS | 1 |  |  |  | [''] | 
| 13 | PLABEL3 | PLABEL3 | 1 |  |  |  | [''] | 
| 14 | PLABEL16 | PLABEL16 | 1 |  |  |  | [''] | 
| 15 | PLABEL6 | PLABEL6 | 1 |  |  |  | [''] | 
| 16 | C6,C5 | 0603-NO | 2 | 47pF |  |  | [''] | 
| 17 | SJ3,SJ1,SJ6,SJ5 | SOLDERJUMPER_CLOSEDWIRE | 4 |  |  |  | [''] | 
| 18 | X2 | M09D | 1 | DE-9 |  |  | [''] | 
| 19 | R2,R1 | 0603-NO | 2 | 10K |  |  | [''] | 
| 20 | MS1 | FEATHERWING_NODIM | 1 | FEATHERWING_NODIM |  |  | [''] | 
| 21 | JP1 | 1X16_ROUND | 1 |  |  |  | [''] | 
| 22 | SW1 | BTN_RKB2_4.6X2.8 | 1 | RKB2 |  |  | [''] | 
| 23 | IC1 | SOIC8_150MIL | 1 | TJA1051T/3 |  |  | [''] | 
| 24 | PLABEL1 | PLABEL1 | 1 |  |  |  | [''] | 
| 25 | R4 | 0603-NO | 1 | 120 |  |  | [''] | 
| 26 | D1 | SOT23 | 1 | PESD1CAN |  |  | [''] | 
| 27 | JP2 | 1X12_ROUND | 1 |  |  |  | [''] | 
| 28 | PLABEL0 | PLABEL0 | 1 |  |  |  | [''] | 
| 29 | PLABEL4 | PLABEL4 | 1 |  |  |  | [''] | 
| 30 | PLABEL5 | PLABEL5 | 1 |  |  |  | [''] | 
| 31 | C3 | 0805-NO | 1 | 1uF |  |  | [''] | 
| 32 | PLABEL10 | PLABEL10 | 1 |  |  |  | [''] | 
| 33 | PLABEL9 | PLABEL9 | 1 |  |  |  | [''] | 
| 34 | U$33 | PCBFEAT-REV-040 | 1 |  |  |  | [''] | 
| 35 | PLABEL8 | PLABEL8 | 1 |  |  |  | [''] | 
| 36 | PLABEL11 | PLABEL11 | 1 |  |  |  | [''] | 
| 37 | PLABEL13 | PLABEL13 | 1 |  |  |  | [''] | 
| 38 | U$22 | FEATHERLOGO | 1 |  |  |  | [''] | 
| 39 | PLABEL12 | PLABEL12 | 1 |  |  |  | [''] | 
| 40 | PLABEL14 | PLABEL14 | 1 |  |  |  | [''] | 

## bom_schematic
| Ref | Qnty | Value | Cmp name | Footprint | Description | Vendor | DNP | 
| --- | --- | --- | --- | --- | --- | --- | --- | 
| C1, C2, C12, C14 | 4 | 10uF | CAP_CERAMIC0805-NOOUTLINE | working:0805-NO |  |  |  | 
| C3 | 1 | 1uF | CAP_CERAMIC0805-NOOUTLINE | working:0805-NO |  |  |  | 
| C5, C6 | 2 | 47pF | CAP_CERAMIC0603_NO | working:0603-NO |  |  |  | 
| C7, C8 | 2 | 15pF | CAP_CERAMIC0603_NO | working:0603-NO |  |  |  | 
| C10, C11, C22 | 3 | 0.1uF | CAP_CERAMIC0603_NO | working:0603-NO |  |  |  | 
| D1 | 1 | PESD1CAN | PESD1CAN | working:SOT23 |  |  |  | 
| FID2, FID3 | 2 | FIDUCIAL_1MM | FIDUCIAL_1MM | working:FIDUCIAL_1MM |  |  |  | 
| IC1 | 1 | TJA1051T/3 | CAN_TRANSCIEVER_TCAN1051V | working:SOIC8_150MIL |  |  |  | 
| IC2 | 1 | MCP2515/SO | MCP2515/SO | working:SOIC18WIDE |  |  |  | 
| JP1 | 1 | HEADER-1X16ROUND | HEADER-1X16ROUND | working:1X16_ROUND |  |  |  | 
| JP2 | 1 | HEADER-1X12 | HEADER-1X12 | working:1X12_ROUND |  |  |  | 
| JP4 | 1 | HEADER-1X4ROUND | HEADER-1X4ROUND | working:1X04_ROUND |  |  |  | 
| MS1 | 1 | FEATHERWING_NODIM | FEATHERWING_NODIM | working:FEATHERWING_NODIM |  |  |  | 
| NEOPIX1 | 1 | 3.5mm | TERMBLOCK_1X3 | working:TERMBLOCK_1X3-3.5MM |  |  |  | 
| R1, R2 | 2 | 10K | RESISTOR_0603_NOOUT | working:0603-NO |  |  |  | 
| R4 | 1 | 120 | RESISTOR_0603_NOOUT | working:0603-NO |  |  |  | 
| SJ1, SJ3, SJ5, SJ6 | 4 | SOLDERJUMPER_CLOSED | SOLDERJUMPER_CLOSED | working:SOLDERJUMPER_CLOSEDWIRE |  |  |  | 
| SW1 | 1 | RKB2 | SWITCH_TACT_SMT_RKB2 | working:BTN_RKB2_4.6X2.8 |  |  |  | 
| U1 | 1 | AP3602 | AP3602 | working:SOT23-6 |  |  |  | 
| X2 | 1 | DE-9 | M09D | working:M09D |  |  |  | 
| Y1 | 1 | 16MHz 9pF | CRYSTAL3.2X2.5 | working:CRYSTAL_3.2X2.5 |  |  |  |

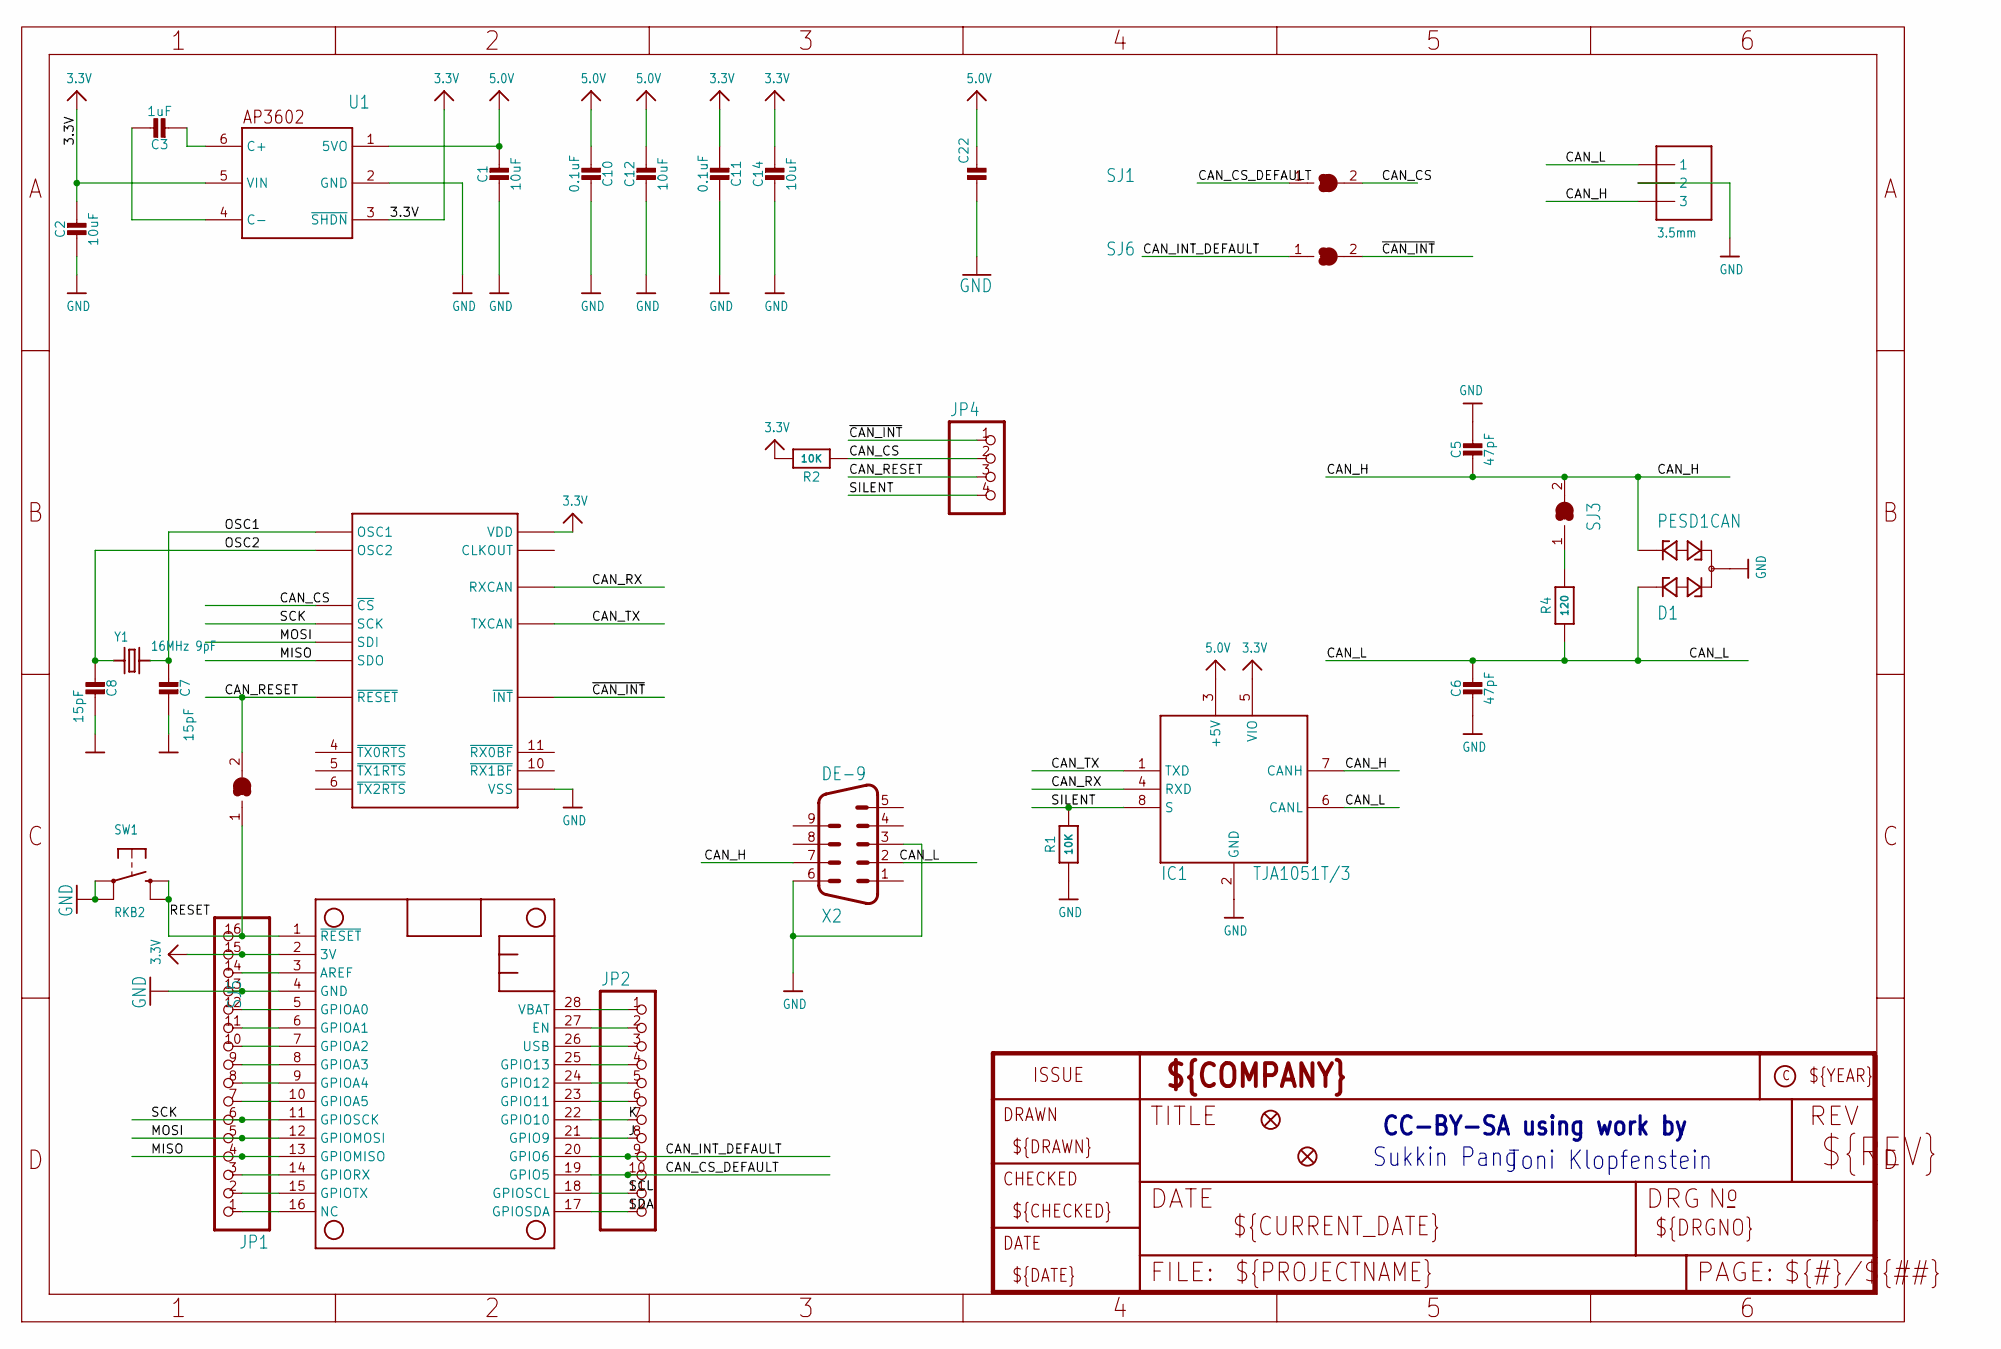
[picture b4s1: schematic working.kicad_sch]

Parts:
C1, C2, C12, C14: 10uF; 0805-NO
C3: 1uF; 0805-NO
C5, C6: 47pF; 0603-NO
C7, C8: 15pF; 0603-NO
C10, C11, C22: 0.1uF; 0603-NO
D1: PESD1CAN; SOT23
FID2, FID3: FIDUCIAL_1MM
IC1: TJA1051T/3; SOIC8_150MIL
IC2: MCP2515/SO; SOIC18WIDE
JP1: HEADER-1X16ROUND; 1X16_ROUND
JP2: HEADER-1X12; 1X12_ROUND
JP4: HEADER-1X4ROUND; 1X04_ROUND
MS1: FEATHERWING_NODIM
NEOPIX1: 3.5mm; TERMBLOCK_1X3-3.5MM
R1, R2: 10K; 0603-NO
R4: 120; 0603-NO
SJ1, SJ3, SJ5, SJ6: SOLDERJUMPER_CLOSED; SOLDERJUMPER_CLOSEDWIRE
SW1: RKB2; BTN_RKB2_4.6X2.8
U1: AP3602; SOT23-6
X2: DE-9; M09D
Y1: 16MHz 9pF; CRYSTAL_3.2X2.5

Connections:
3.3V: C2.1, C11.2, C14.1, IC1.5 (VIO), IC2.18 (VDD), JP1.15, MS1.2 (3V), R2.2, U1.3 (~SHDN), U1.5 (VIN)
5.0V: C1.1, C10.2, C12.1, C22.2, IC1.3 (+5V), U1.1 (5VO)
A: JP1.12, MS1.5 (GPIOA0)
AREF: JP1.14, MS1.3 (AREF)
B: JP1.11, MS1.6 (GPIOA1)
C: JP1.10, MS1.7 (GPIOA2)
CAN_CS: IC2.16 (~CS), JP4.2, R2.1, SJ1.2
CAN_CS_DEFAULT: JP2.10, MS1.19 (GPIO5), SJ1.1
CAN_H: C5.2, D1.2, IC1.7 (CANH), NEOPIX1.3, SJ3.2, X2.7
CAN_INT_DEFAULT: JP2.9, MS1.20 (GPIO6), SJ6.1
CAN_L: C6.1, D1.1, IC1.6 (CANL), NEOPIX1.1, R4.1, X2.2
CAN_RESET: IC2.17 (~RESET), JP4.3, SJ5.2
CAN_RX: IC1.4 (RXD), IC2.2 (RXCAN)
CAN_TX: IC1.1 (TXD), IC2.1 (TXCAN)
D: JP1.9, MS1.8 (GPIOA3)
E: JP1.8, MS1.9 (GPIOA4)
EN: JP2.2, MS1.27 (EN)
F: JP1.7, MS1.10 (GPIOA5)
G: JP1.1, MS1.16 (NC)
GND: C1.2, C2.2, C5.1, C6.2, C7.1, C8.1, C10.1, C11.1, C12.2, C14.2, C22.1, D1.3, IC1.2 (GND), IC2.9 (VSS), JP1.13, MS1.4 (GND), NEOPIX1.2, R1.1, SW1.A, SW1.A' (P1), U1.2 (GND), X2.3, X2.6
J: JP2.8, MS1.21 (GPIO9)
K: JP2.7, MS1.22 (GPIO10)
L: JP2.6, MS1.23 (GPIO11)
M: JP2.5, MS1.24 (GPIO12)
MISO: IC2.15 (SDO), JP1.4, MS1.13 (GPIOMISO)
MOSI: IC2.14 (SDI), JP1.5, MS1.12 (GPIOMOSI)
N: JP2.4, MS1.25 (GPIO13)
unnamed: C3.2, U1.6 (C+)
unnamed: C3.1, U1.4 (C-)
unnamed: R4.2, SJ3.1
OSC1: C7.2, IC2.8 (OSC1), Y1.2
OSC2: C8.2, IC2.7 (OSC2), Y1.1
RESET: JP1.16, MS1.1 (~RESET), SJ5.1, SW1.B (S), SW1.B' (S1)
RX: JP1.3, MS1.14 (GPIORX)
SCK: IC2.13 (SCK), JP1.6, MS1.11 (GPIOSCK)
SCL: JP2.11, MS1.18 (GPIOSCL)
SDA: JP2.12, MS1.17 (GPIOSDA)
SILENT: IC1.8 (S), JP4.4, R1.2
TX: JP1.2, MS1.15 (GPIOTX)
USB: JP2.3, MS1.26 (USB)
VBAT: JP2.1, MS1.28 (VBAT)
~CAN_INT: IC2.12 (~INT), JP4.1, SJ6.2

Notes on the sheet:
Toni Klopfenstein
CC-BY-SA using work by
Sukkin Pang
